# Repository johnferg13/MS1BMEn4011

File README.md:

Schematic, gerbers, and drill file for MS1. Please let me know if you need any other documentation. Thanks!

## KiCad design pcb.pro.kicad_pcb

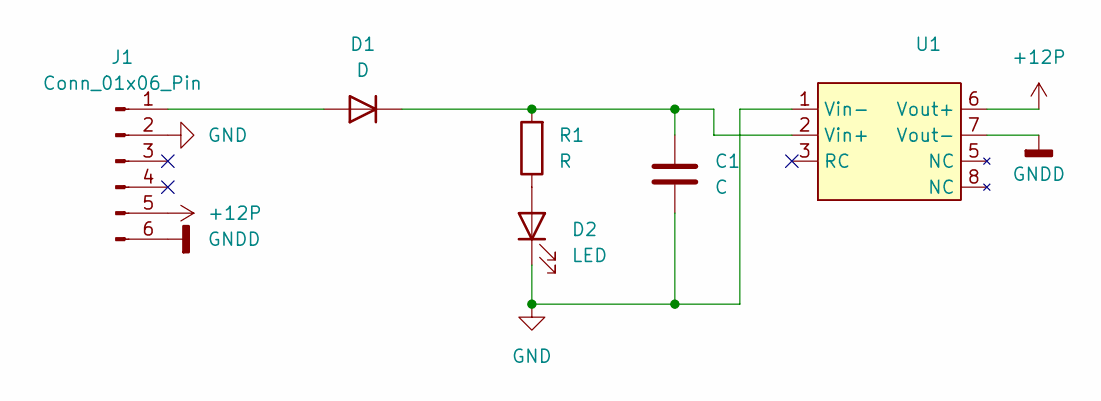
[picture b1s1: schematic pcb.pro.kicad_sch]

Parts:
C1: C; C_0805_2012Metric_Pad1.18x1.45mm_HandSolder
D1: D; D_SMA
D2: LED; LED_0805_2012Metric
J1: Conn_01x06_Pin; Molex_Micro-Fit_3.0_43045-0612_2x03_P3.00mm_Vertical
R1: R; R_1206_3216Metric
U1: SPAN02

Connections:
+12P: J1.5, U1.6 (Vout+)
GND: C1.2, D2.1 (K), J1.2, U1.1 (Vin-)
GNDD: J1.6, U1.7 (Vout-)
unnamed: D1.2 (A), J1.1
unnamed: C1.1, D1.1 (K), R1.2, U1.2 (Vin+)
unnamed: D2.2 (A), R1.1

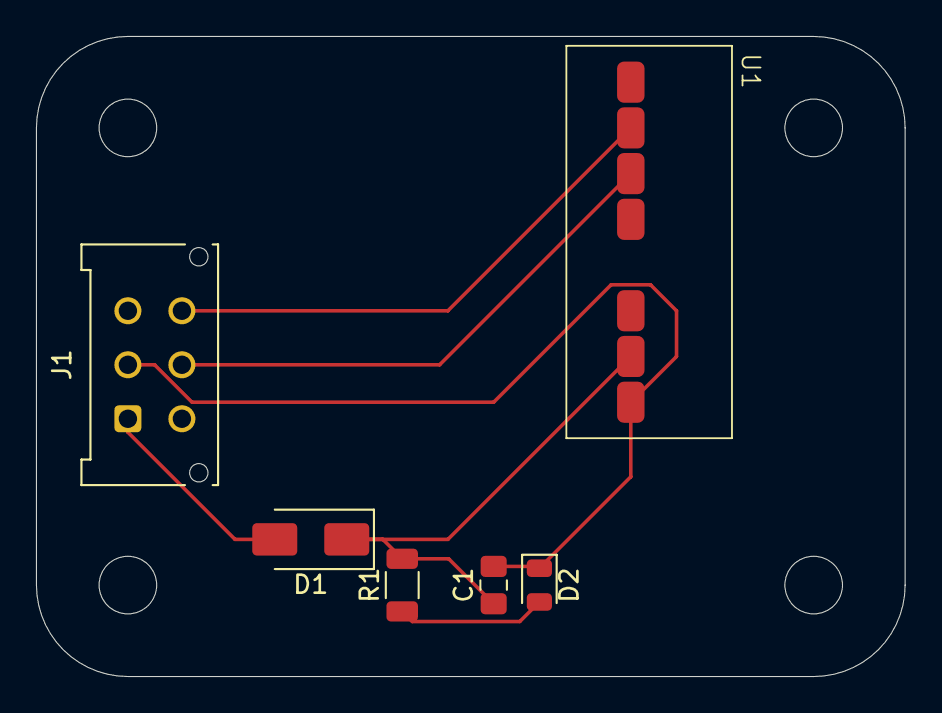
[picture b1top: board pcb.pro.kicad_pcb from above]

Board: 2 copper layers, 48.3 x 35.6 mm, 6 parts (0 on the bottom side), 6 nets.
